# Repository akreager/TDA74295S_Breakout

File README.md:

# TDA7429 Breakout Board & Arduino Library

Breakout board and Arduino library for the ST TDA7429 digitally controlled audio processor with surround sound matrix.

## What is the TDA7429?

The TDA7429 is an I²C-controlled audio DSP designed for TV and Hi-Fi systems. It handles input selection, volume/tone control, surround sound processing, and speaker balance — all through a two-wire serial bus with no external microcontroller overhead beyond simple register writes.

**Key specs:**
- 3 stereo inputs with 0–31.5 dB attenuation (0.5 dB steps)
- Bass, middle, and treble control (±14 dB, 2 dB steps)
- 4 independent speaker attenuators (0–79 dB, 1 dB steps + mute)
- 3 surround modes: music, movie, simulated (256 selectable responses)
- 4 programmable phase shifters
- Monitor and auxiliary outputs
- 106 dB signal-to-noise ratio
- 7–10.2 V supply

## Repository Structure

```
├── pcb/
│   ├── TDA7429_BREAKOUT.kicad_pro      # KiCad project
│   ├── TDA7429_BREAKOUT.kicad_sch      # Schematic
│   ├── TDA7429_BREAKOUT.kicad_pcb      # PCB layout
│   ├── fp-lib-table                    # Footprint library table
│   ├── sym-lib-table                   # Symbol library table
│   ├── eagle2kicad_pcb.py              # Board conversion script
│   ├── eagle2kicad_sch.py              # Schematic conversion script
│   ├── TDA7429_KiCad_Lib/             # Custom KiCad library
│   │   ├── TDA7429.kicad_sym
│   │   └── TDA7429.pretty/
│   │       └── SDIP-42_W15.24mm_P1.778mm.kicad_mod
│   └── Archive Eagle Design/           # Original Eagle 6.5 files
│       ├── TDA7429_BREAKOUT.sch
│       ├── TDA7429_BREAKOUT.brd
│       └── TDA7429_BREAKOUT.pdf
├── TDA7429S TDA7429T.pdf               # Datasheet
├── .gitattributes
├── .gitignore
└── README.md
```

## Hardware

### Breakout Board

~50 × 50 mm board carrying the TDA7429S (SDIP-42) with all external filter components from the datasheet reference circuit. Pin headers break out:

| Header     | Pins                                      |
|------------|-------------------------------------------|
| AUDIO_IN   | 3 stereo input pairs (L/R × IN1–IN3)     |
| AUDIO_OUT  | L_OUT, R_OUT, AUXOUT_L, AUXOUT_R          |
| MONITOR    | MONITOR_L, MONITOR_R                      |
| DATA       | SDA, SCL                                  |
| POWER      | +9V, GND                                  |

### Connecting to Arduino

| Breakout | Arduino Uno/Nano | Arduino Mega |
|----------|------------------|--------------|
| SDA      | A4               | 20           |
| SCL      | A5               | 21           |
| GND      | GND              | GND          |

The TDA7429 runs at 7–10.2 V — do **not** power it from the Arduino 5V pin. Use a separate 9V supply for the breakout board. The I²C bus needs pull-up resistors to the Arduino's 3.3V or 5V (4.7kΩ typical). The chip's I²C thresholds (V_IL max 1V, V_IH min 3V) are compatible with both 3.3V and 5V logic.

## Arduino Library

### Installation

Copy the `firmware/TDA7429/` folder into your Arduino libraries directory, or use the Arduino IDE Library Manager if published.

### Quick Start

```cpp
#include <Wire.h>
#include <TDA7429.h>

TDA7429 audio;

void setup() {
  Wire.begin();
  audio.begin();

  audio.selectInput(1);          // Input 1
  audio.setInputAttenuation(0);  // 0 dB (no attenuation)
  audio.setBass(0);              // Flat
  audio.setMiddle(0);            // Flat
  audio.setTreble(0);            // Flat
  audio.setSpeakerAttenuation(TDA7429_LEFT, -20);   // -20 dB
  audio.setSpeakerAttenuation(TDA7429_RIGHT, -20);  // -20 dB
  audio.setSurroundMode(TDA7429_SURROUND_OFF);
}

void loop() {
  // Adjust volume, tone, etc. from serial commands, buttons, encoder...
}
```

### API Reference

| Method | Description |
|--------|-------------|
| `begin()` | Initialize with default (muted) state |
| `selectInput(1–4)` | Choose stereo input pair |
| `setInputAttenuation(dB)` | 0 to -31.5 dB in 0.5 dB steps |
| `setBass(dB)` | -14 to +14 dB in 2 dB steps |
| `setMiddle(dB)` | -14 to +14 dB in 2 dB steps |
| `setTreble(dB)` | -14 to +14 dB in 2 dB steps |
| `setSpeakerAttenuation(ch, dB)` | 0 to -79 dB per channel, 1 dB steps |
| `setAuxAttenuation(ch, dB)` | 0 to -79 dB per channel, 1 dB steps |
| `setSurroundMode(mode)` | OFF, MUSIC, MOVIE, SIMULATED |
| `setEffectControl(dB)` | -6 to -21 dB surround effect level |
| `setPhaseShifters(...)` | Configure 4 phase shift resistors |
| `mute()` / `unmute()` | Mute/unmute all speaker outputs |

## Known Issues / TODO

- [ ] DIG_GND (pin 28) needs to be connected to ground in the schematic
- [ ] Audio connector ground pins (L-, R-) need explicit connection to AGND
- [ ] Consider adding bottom ground pour for improved noise performance
- [ ] Add ferrite bead between DIG_GND and AGND for digital/analog isolation

## License

Hardware design files are released under [CERN-OHL-P v2](https://ohwr.org/cern_ohl_p_v2.txt). Arduino library is released under the MIT License. See individual directories for details.

## Credits

Board design by Allen Kreager. Originally designed in Eagle 6.5, converted to KiCad 7.

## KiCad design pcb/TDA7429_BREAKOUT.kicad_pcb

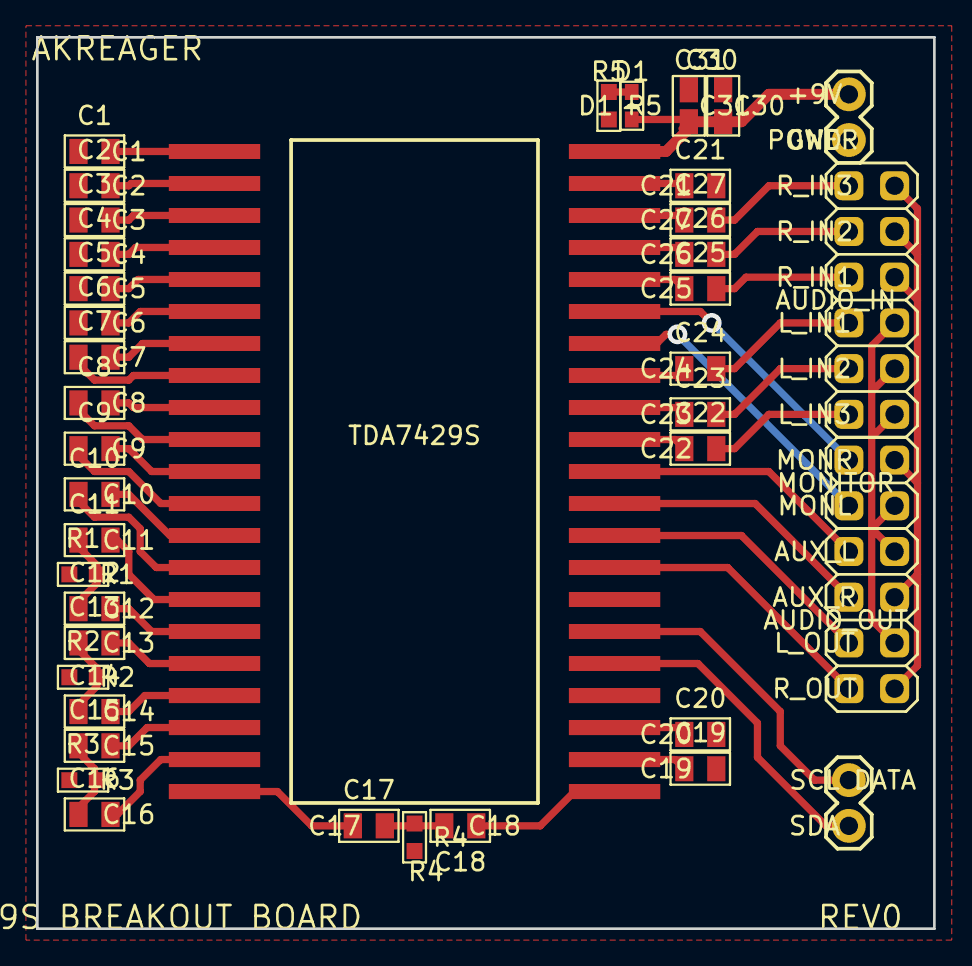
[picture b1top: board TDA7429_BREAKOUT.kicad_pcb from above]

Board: 2 copper layers, 49.8 x 49.5 mm, 42 parts (0 on the bottom side), 54 nets.

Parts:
AUDIO_IN: 2X06
AUDIO_OUT: 2X04
C1, C2, C15, C17: 22nF; C0805
C3: 4.7nF; C0805
C4, C11, C12, C13, C14, C30: 100nF; C0805
C5: 1.2nF; C0805
C6, C19, C20: 5.6nF; C0805
C7: 680nF; C0805
C8, C9, C10: 2.2uF; C0805
C16, C18: 18nF; C0805
C21: 22uF; C0805
C22, C23, C24, C25, C26, C27: 0.47uF; C0805
C31: 10uF; C0805
D1: LED0603
DATA: 1X02
FRAME1: FRAME-LETTER; CREATIVE_COMMONS
MONITOR: 2X02
POWER: 1X02
R1, R2: 5.6K; R0603
R3, R4: 2.7K; R0603
R5: 220; R0603
TDA7429S: TDA7429S_SURFACE; SDIP42_SURFACE

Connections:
+9V: C30.2, C31.2, D1.+, POWER.2, TDA7429S.42
AUXOUT_L: AUDIO_OUT.8, TDA7429S.32
AUXOUT_R: AUDIO_OUT.6, TDA7429S.31
GND: C1.1, C2.1, C3.1, C4.1, C5.1, C6.1, C19.2, C20.2, C21.2, C30.1, C31.1, POWER.1, R1.1, R2.1, R3.1, R4.2, R5.2, TDA7429S.25
HP1: C7.2, TDA7429S.7
L-: AUDIO_IN.1, AUDIO_IN.3, AUDIO_IN.5, AUDIO_OUT.3, AUDIO_OUT.7, MONITOR.1
L_IN1: AUDIO_IN.6, C24.2
L_IN2: AUDIO_IN.4, C23.2
L_IN3: AUDIO_IN.2, C22.2
L_OUT: AUDIO_OUT.4, TDA7429S.30
MONITOR_L: MONITOR.2, TDA7429S.36
MONITOR_R: MONITOR.4, TDA7429S.37
unnamed: D1.-, R5.1
unnamed: C9.1, TDA7429S.12
unnamed: C3.2, TDA7429S.3
unnamed: C1.2, TDA7429S.1
unnamed: C2.2, TDA7429S.2
unnamed: C4.2, TDA7429S.4
unnamed: C5.2, TDA7429S.5
unnamed: C6.2, TDA7429S.6
unnamed: C7.1, TDA7429S.8
unnamed: C8.1, TDA7429S.10
unnamed: C10.1, TDA7429S.14
unnamed: C11.2, TDA7429S.15
unnamed: C11.1, C12.1, R1.2
unnamed: C12.2, TDA7429S.16
unnamed: C13.2, TDA7429S.17
unnamed: C13.1, C14.1, R2.2
unnamed: C14.2, TDA7429S.18
unnamed: C15.2, TDA7429S.19
unnamed: C16.2, TDA7429S.20
unnamed: C15.1, C16.1, R3.2
unnamed: C17.1, TDA7429S.21
unnamed: C18.1, TDA7429S.22
unnamed: C17.2, C18.2, R4.1
unnamed: C19.1, TDA7429S.23
unnamed: C20.1, TDA7429S.24
unnamed: C27.1, TDA7429S.40
unnamed: C26.1, TDA7429S.39
unnamed: C25.1, TDA7429S.38
unnamed: C24.1, TDA7429S.35
unnamed: C23.1, TDA7429S.34
unnamed: C22.1, TDA7429S.33
unnamed: C21.1, TDA7429S.41
R-: AUDIO_IN.7, AUDIO_IN.9, AUDIO_IN.11, AUDIO_OUT.1, AUDIO_OUT.5, MONITOR.3
REAROUT: C8.2, TDA7429S.9
R_IN1: AUDIO_IN.8, C25.2
R_IN2: AUDIO_IN.10, C26.2
R_IN3: AUDIO_IN.12, C27.2
R_OUT: AUDIO_OUT.2, TDA7429S.29
SCL: DATA.1, TDA7429S.27
SDA: DATA.2, TDA7429S.26
VAR_L: C9.2, TDA7429S.11
VAR_R: C10.2, TDA7429S.13

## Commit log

2015-08-07 :circus_tent: Added .gitattributes & .gitignore files
2015-08-07 TDA7429 audio DSP IC breakout board
2015-08-08 TDA7429 datasheet
2026-03-07 revive project and prepare for migration to kicad design and arduino library
2026-03-07 add readme
2026-03-07 inital kicad conversion
2026-03-07 Update project directory structure
2026-03-07 Add symbol that matches datasheet test circuit.
2026-03-07 start redesigning schematic
2026-03-08 update schematic
2026-03-08 tweak schematic, add i2c pullup resistors.
2026-03-09 add reference docs
